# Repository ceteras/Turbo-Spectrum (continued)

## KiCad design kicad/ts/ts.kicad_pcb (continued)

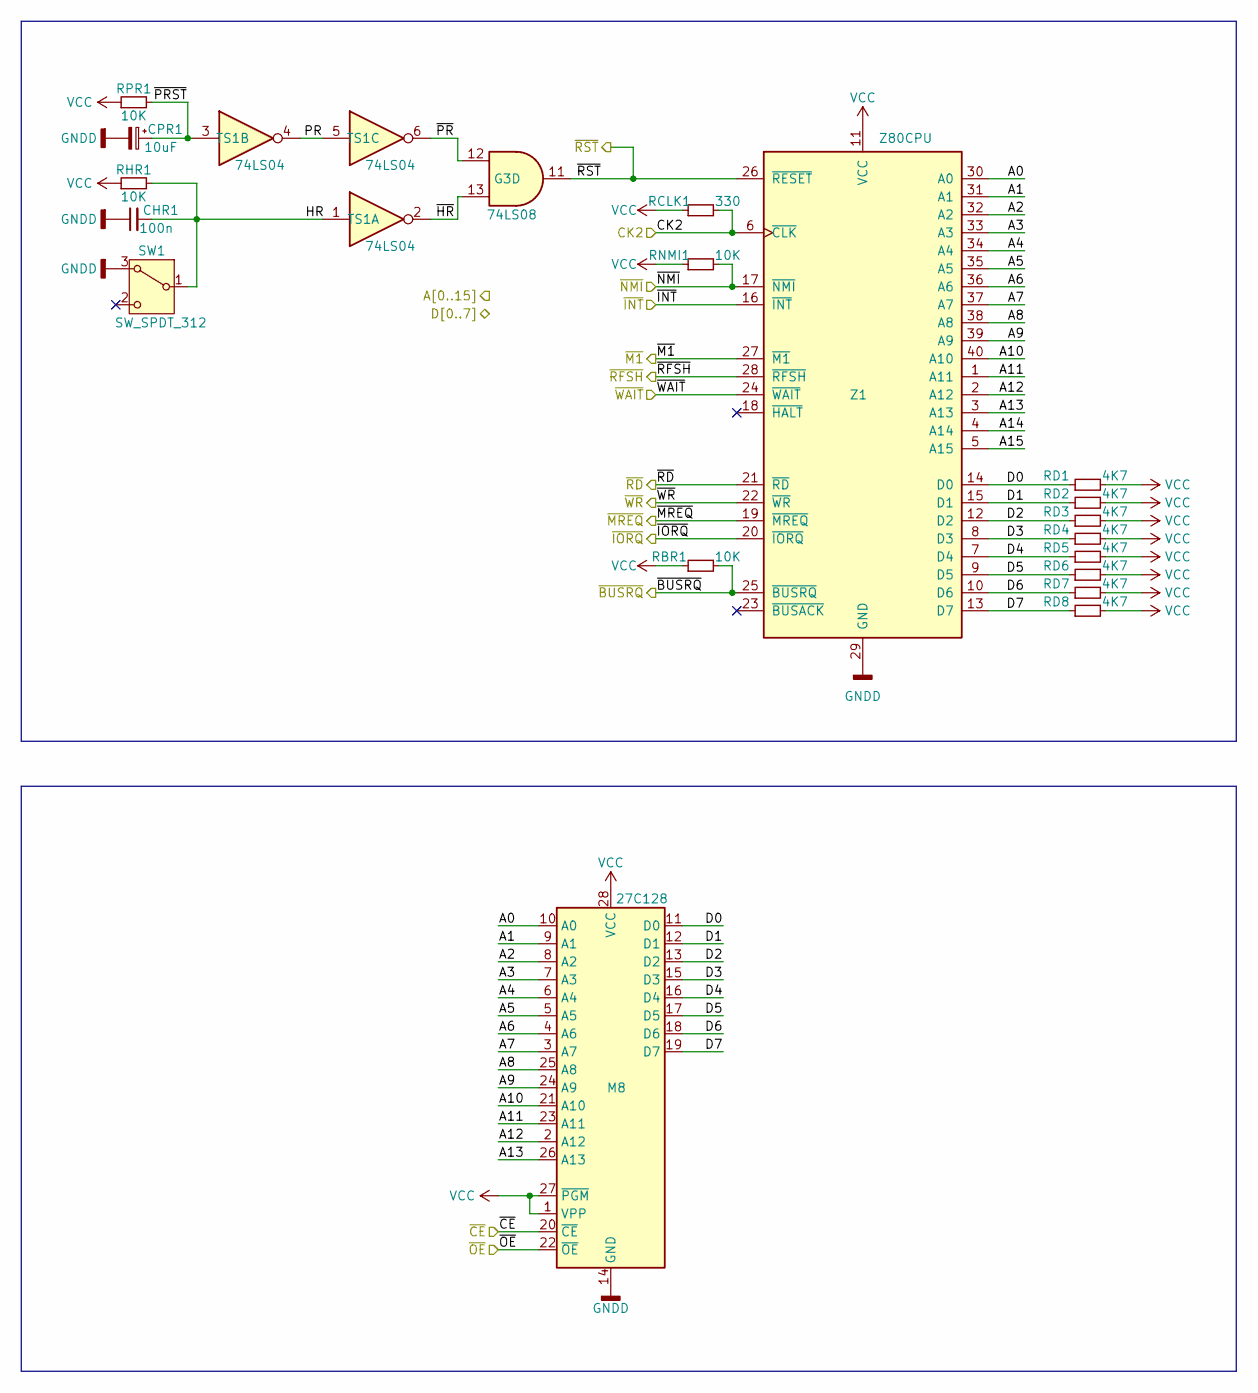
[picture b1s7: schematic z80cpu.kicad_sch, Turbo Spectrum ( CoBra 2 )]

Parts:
CHR1: 100n; C_Disc_D3.0mm_W1.6mm_P2.50mm
CPR1: 10uF; CP_Radial_D5.0mm_P2.00mm
G3: 74LS08; DIP-14_W7.62mm
M8: 27C128; DIP-28_W15.24mm
RBR1: 10K; R_Axial_DIN0204_L3.6mm_D1.6mm_P7.62mm_Horizontal
RCLK1: 330; R_Axial_DIN0204_L3.6mm_D1.6mm_P7.62mm_Horizontal
RD1, RD2, RD3, RD4, RD5, RD6, RD7, RD8: 4K7; R_Axial_DIN0204_L3.6mm_D1.6mm_P7.62mm_Horizontal
RHR1: 10K; R_Axial_DIN0204_L3.6mm_D1.6mm_P7.62mm_Horizontal
RNMI1: 10K; R_Axial_DIN0204_L3.6mm_D1.6mm_P7.62mm_Horizontal
RPR1: 10K; R_Axial_DIN0204_L3.6mm_D1.6mm_P7.62mm_Horizontal
SW1: SW_SPDT_312; SW_XKB_DM1-16UC-1
TS1: 74LS04; DIP-14_W7.62mm
Z1: Z80CPU; DIP-40_W15.24mm

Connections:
/A0: M8.10 (A0), Z1.30 (A0); also elsewhere on the board
/A1: M8.9 (A1), Z1.31 (A1); also elsewhere on the board
/A2: M8.8 (A2), Z1.32 (A2); also elsewhere on the board
/A3: M8.7 (A3), Z1.33 (A3); also elsewhere on the board
/A4: M8.6 (A4), Z1.34 (A4); also elsewhere on the board
/A5: M8.5 (A5), Z1.35 (A5); also elsewhere on the board
/A6: M8.4 (A6), Z1.36 (A6); also elsewhere on the board
/A7: M8.3 (A7), Z1.37 (A7); also elsewhere on the board
/A8: M8.25 (A8), Z1.38 (A8); also elsewhere on the board
/A9: M8.24 (A9), Z1.39 (A9); also elsewhere on the board
/A10: M8.21 (A10), Z1.40 (A10); also elsewhere on the board
/A11: M8.23 (A11), Z1.1 (A11); also elsewhere on the board
/A12: M8.2 (A12), Z1.2 (A12); also elsewhere on the board
/A13: M8.26 (A13), Z1.3 (A13); also elsewhere on the board
/A14: Z1.4 (A14); also elsewhere on the board
/A15: Z1.5 (A15); also elsewhere on the board
/CK2: RCLK1.2, Z1.6 (~CLK); also elsewhere on the board
/D0: M8.11 (D0), RD1.1, Z1.14 (D0); also elsewhere on the board
/D1: M8.12 (D1), RD2.1, Z1.15 (D1); also elsewhere on the board
/D2: M8.13 (D2), RD3.1, Z1.12 (D2); also elsewhere on the board
/D3: M8.15 (D3), RD4.1, Z1.8 (D3); also elsewhere on the board
/D4: M8.16 (D4), RD5.1, Z1.7 (D4); also elsewhere on the board
/D5: M8.17 (D5), RD6.1, Z1.9 (D5); also elsewhere on the board
/D6: M8.18 (D6), RD7.1, Z1.10 (D6); also elsewhere on the board
/D7: M8.19 (D7), RD8.1, Z1.13 (D7); also elsewhere on the board
/TIMING & CTRL/~CE: M8.20 (~CE); also elsewhere on the board
/TIMING & CTRL/~OE: M8.22 (~OE); also elsewhere on the board
/TIMING & CTRL/~WAIT: Z1.24 (~WAIT); also elsewhere on the board
/Z80CPU & ROM/HR: CHR1.2, RHR1.2, SW1.1 (B), TS1.1
/Z80CPU & ROM/PR: TS1.4, TS1.5
/Z80CPU & ROM/~HR: G3.13, TS1.2
/Z80CPU & ROM/~PRST: CPR1.1, RPR1.2, TS1.3
/Z80CPU & ROM/~PR: G3.12, TS1.6
/~BUSRQ: RBR1.2, Z1.25 (~BUSRQ)
/~INT: Z1.16 (~INT)
/~IORQ: Z1.20 (~IORQ); also elsewhere on the board
/~M1: Z1.27 (~M1)
/~MREQ: Z1.19 (~MREQ); also elsewhere on the board
/~NMI: RNMI1.2, Z1.17 (~NMI)
/~RD: Z1.21 (~RD); also elsewhere on the board
/~RFSH: Z1.28 (~RFSH); also elsewhere on the board
/~RST: G3.11, Z1.26 (~RESET); also elsewhere on the board
/~WR: Z1.22 (~WR); also elsewhere on the board
GNDD: CHR1.1, CPR1.2, M8.14 (GND), SW1.3 (A), Z1.29 (GND); also elsewhere on the board
VCC: M8.1 (VPP), M8.27 (~PGM), M8.28 (VCC), RBR1.1, RCLK1.1, RD1.2, RD2.2, RD3.2, RD4.2, RD5.2, RD6.2, RD7.2, RD8.2, RHR1.1, RNMI1.1, RPR1.1, Z1.11 (VCC); also elsewhere on the board

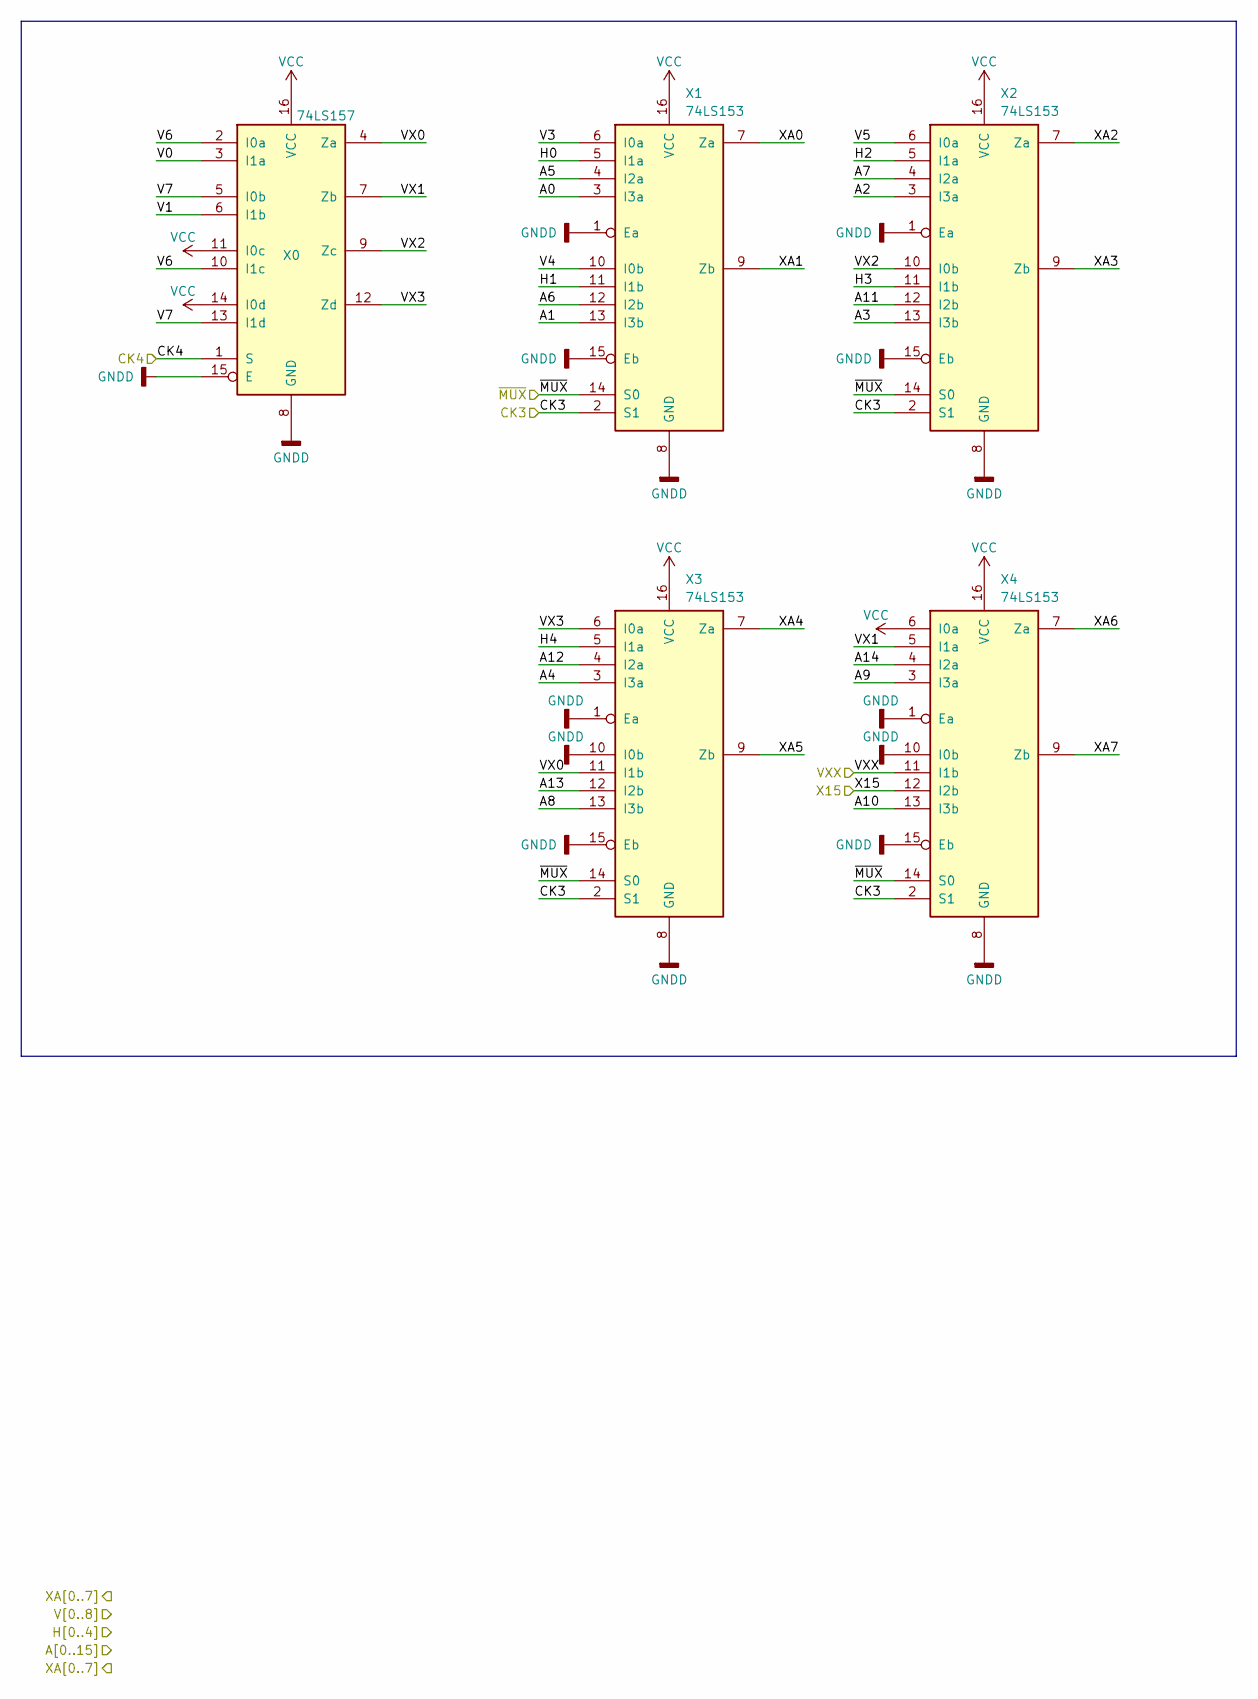
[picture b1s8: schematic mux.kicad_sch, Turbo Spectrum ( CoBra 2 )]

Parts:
X0: 74LS157; DIP-16_W7.62mm
X1, X2, X3, X4: 74LS153; DIP-16_W7.62mm

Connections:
/A0: X1.3 (I3a); also elsewhere on the board
/A1: X1.13 (I3b); also elsewhere on the board
/A2: X2.3 (I3a); also elsewhere on the board
/A3: X2.13 (I3b); also elsewhere on the board
/A4: X3.3 (I3a); also elsewhere on the board
/A5: X1.4 (I2a); also elsewhere on the board
/A6: X1.12 (I2b); also elsewhere on the board
/A7: X2.4 (I2a); also elsewhere on the board
/A8: X3.13 (I3b); also elsewhere on the board
/A9: X4.3 (I3a); also elsewhere on the board
/A10: X4.13 (I3b); also elsewhere on the board
/A11: X2.12 (I2b); also elsewhere on the board
/A12: X3.4 (I2a); also elsewhere on the board
/A13: X3.12 (I2b); also elsewhere on the board
/A14: X4.4 (I2a); also elsewhere on the board
/CK3: X1.2 (S1), X2.2 (S1), X3.2 (S1), X4.2 (S1); also elsewhere on the board
/CK4: X0.1 (S); also elsewhere on the board
/DRAM/XA0: X1.7 (Za); also elsewhere on the board
/DRAM/XA1: X1.9 (Zb); also elsewhere on the board
/DRAM/XA2: X2.7 (Za); also elsewhere on the board
/DRAM/XA3: X2.9 (Zb); also elsewhere on the board
/DRAM/XA4: X3.7 (Za); also elsewhere on the board
/DRAM/XA5: X3.9 (Zb); also elsewhere on the board
/DRAM/XA6: X4.7 (Za); also elsewhere on the board
/DRAM/XA7: X4.9 (Zb); also elsewhere on the board
/MUX/H0: X1.5 (I1a); also elsewhere on the board
/MUX/H1: X1.11 (I1b); also elsewhere on the board
/MUX/H2: X2.5 (I1a); also elsewhere on the board
/MUX/H3: X2.11 (I1b); also elsewhere on the board
/MUX/H4: X3.5 (I1a); also elsewhere on the board
/MUX/V0: X0.3 (I1a); also elsewhere on the board
/MUX/V1: X0.6 (I1b); also elsewhere on the board
/MUX/V3: X1.6 (I0a); also elsewhere on the board
/MUX/V4: X1.10 (I0b); also elsewhere on the board
/MUX/V5: X2.6 (I0a); also elsewhere on the board
/MUX/V6: X0.2 (I0a), X0.10 (I1c); also elsewhere on the board
/MUX/V7: X0.5 (I0b), X0.13 (I1d); also elsewhere on the board
/MUX/VX0: X0.4 (Za), X3.11 (I1b)
/MUX/VX1: X0.7 (Zb), X4.5 (I1a)
/MUX/VX2: X0.9 (Zc), X2.10 (I0b)
/MUX/VX3: X0.12 (Zd), X3.6 (I0a)
/MUX/VXX: X4.11 (I1b); also elsewhere on the board
/MUX/X15: X4.12 (I2b); also elsewhere on the board
/MUX/~MUX: X1.14 (S0), X2.14 (S0), X3.14 (S0), X4.14 (S0); also elsewhere on the board
GNDD: X0.8 (GND), X0.15 (E), X1.1 (Ea), X1.8 (GND), X1.15 (Eb), X2.1 (Ea), X2.8 (GND), X2.15 (Eb), X3.1 (Ea), X3.8 (GND), X3.10 (I0b), X3.15 (Eb), X4.1 (Ea), X4.8 (GND), X4.10 (I0b), X4.15 (Eb); also elsewhere on the board
VCC: X0.11 (I0c), X0.14 (I0d), X0.16 (VCC), X1.16 (VCC), X2.16 (VCC), X3.16 (VCC), X4.6 (I0a), X4.16 (VCC); also elsewhere on the board

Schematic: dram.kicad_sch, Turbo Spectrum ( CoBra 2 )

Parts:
L1: 74LS373; DIP-20_W7.62mm
M0, M1, M2, M3, M4, M5, M6, M7: MMN4164; DIP-16_W7.62mm
R0: 0; R_Axial_DIN0204_L3.6mm_D1.6mm_P7.62mm_Horizontal

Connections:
/CK3D: L1.1 (OE); also elsewhere on the board
/D0: L1.2 (O0), M0.14 (Q); also elsewhere on the board
/D1: L1.5 (O1), M1.14 (Q); also elsewhere on the board
/D2: L1.6 (O2), M2.14 (Q); also elsewhere on the board
/D3: L1.9 (O3), M3.14 (Q); also elsewhere on the board
/D4: L1.12 (O4), M4.14 (Q); also elsewhere on the board
/D5: L1.15 (O5), M5.14 (Q); also elsewhere on the board
/D6: L1.16 (O6), M6.14 (Q); also elsewhere on the board
/D7: L1.19 (O7), M7.14 (Q); also elsewhere on the board
/DRAM/XA0: M0.5 (A0), M1.5 (A0), M2.5 (A0), M3.5 (A0), M4.5 (A0), M5.5 (A0), M6.5 (A0), M7.5 (A0); also elsewhere on the board
/DRAM/XA1: M0.6 (A1), M1.6 (A1), M2.6 (A1), M3.6 (A1), M4.6 (A1), M5.6 (A1), M6.6 (A1), M7.6 (A1); also elsewhere on the board
/DRAM/XA2: M0.7 (A2), M1.7 (A2), M2.7 (A2), M3.7 (A2), M4.7 (A2), M5.7 (A2), M6.7 (A2), M7.7 (A2); also elsewhere on the board
/DRAM/XA3: M0.12 (A3), M1.12 (A3), M2.12 (A3), M3.12 (A3), M4.12 (A3), M5.12 (A3), M6.12 (A3), M7.12 (A3); also elsewhere on the board
/DRAM/XA4: M0.11 (A4), M1.11 (A4), M2.11 (A4), M3.11 (A4), M4.11 (A4), M5.11 (A4), M6.11 (A4), M7.11 (A4); also elsewhere on the board
/DRAM/XA5: M0.10 (A5), M1.10 (A5), M2.10 (A5), M3.10 (A5), M4.10 (A5), M5.10 (A5), M6.10 (A5), M7.10 (A5); also elsewhere on the board
/DRAM/XA6: M0.13 (A6), M1.13 (A6), M2.13 (A6), M3.13 (A6), M4.13 (A6), M5.13 (A6), M6.13 (A6), M7.13 (A6); also elsewhere on the board
/DRAM/XA7: M0.9 (A7), M1.9 (A7), M2.9 (A7), M3.9 (A7), M4.9 (A7), M5.9 (A7), M6.9 (A7), M7.9 (A7); also elsewhere on the board
/DRAM/XA8: M0.1 (A8NC), M1.1 (A8NC), M2.1 (A8NC), M3.1 (A8NC), M4.1 (A8NC), M5.1 (A8NC), M6.1 (A8NC), M7.1 (A8NC), R0.2
/MD0: L1.3 (D0), M0.2 (D); also elsewhere on the board
/MD1: L1.4 (D1), M1.2 (D); also elsewhere on the board
/MD2: L1.7 (D2), M2.2 (D); also elsewhere on the board
/MD3: L1.8 (D3), M3.2 (D); also elsewhere on the board
/MD4: L1.13 (D4), M4.2 (D); also elsewhere on the board
/MD5: L1.14 (D5), M5.2 (D); also elsewhere on the board
/MD6: L1.17 (D6), M6.2 (D); also elsewhere on the board
/MD7: L1.18 (D7), M7.2 (D); also elsewhere on the board
/~CAS: M0.15 (~CAS), M1.15 (~CAS), M2.15 (~CAS), M3.15 (~CAS), M4.15 (~CAS), M5.15 (~CAS), M6.15 (~CAS), M7.15 (~CAS); also elsewhere on the board
/~DRD: L1.11 (LE); also elsewhere on the board
/~RAS: M0.4 (~RAS), M1.4 (~RAS), M2.4 (~RAS), M3.4 (~RAS), M4.4 (~RAS), M5.4 (~RAS), M6.4 (~RAS), M7.4 (~RAS); also elsewhere on the board
/~WE: M0.3 (~WR), M1.3 (~WR), M2.3 (~WR), M3.3 (~WR), M4.3 (~WR), M5.3 (~WR), M6.3 (~WR), M7.3 (~WR); also elsewhere on the board
GNDD: L1.10 (GND), M0.16 (GND), M1.16 (GND), M2.16 (GND), M3.16 (GND), M4.16 (GND), M5.16 (GND), M6.16 (GND), M7.16 (GND), R0.1; also elsewhere on the board
VCC: L1.20 (VCC), M0.8 (VCC), M1.8 (VCC), M2.8 (VCC), M3.8 (VCC), M4.8 (VCC), M5.8 (VCC), M6.8 (VCC), M7.8 (VCC); also elsewhere on the board

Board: 2 copper layers, 133 parts (0 on the bottom side), 185 nets, no tracks yet.

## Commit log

2024-12-26 Initial commit.
2024-12-26 edit readme
2024-12-26 update footprints
2024-12-27 Schemativ corrections, work started on pcb
2024-12-27 More pcb work
2024-12-27 Schematic corrections, more traces to pcb, update to DIN 3x32 connector footprint
2024-12-27 Schematic corrections, more traces to pcb
2024-12-27 4164 footprint corrected, more pcb traces
2024-12-28 Schematic corrections, add more pcb traces
2024-12-28 Schematic corrections, all pcb traces placed, todo footprints check
2024-12-28 Last schema & pcb corrections, DRC passed, some warnings todo
2024-12-28 Add mounting holes, update README, new image
2024-12-28 update pdf to the latest schematic
2024-12-28 minor updates
2024-12-28 new render
2024-12-28 Changed VGA connector to Amphenol L77HDE15SD1CH4FVGA
2024-12-28 add licence file for the VGA 3D model
2024-12-28 remove VGA 3D model
